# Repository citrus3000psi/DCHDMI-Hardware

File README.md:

# DCHDMI-Hardware
Hardware Design for Chriz2600 Dreamcast Firmware found at https://github.com/chriz2600/DreamcastHDMI/

This Git will include hardware version 1.3a and any future versions.

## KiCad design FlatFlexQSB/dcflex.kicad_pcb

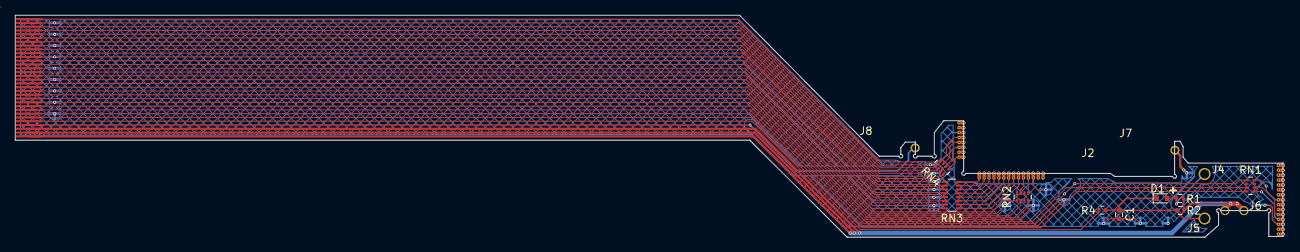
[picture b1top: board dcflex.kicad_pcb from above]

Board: 2 copper layers, 167.6 x 29.3 mm, 17 parts (0 on the bottom side), 42 nets.

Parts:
C1: .1u; C_0402
D1: 1N4148WT; D_SOD-523
J1: Conn_01x32_Male; DC_FLEX_FFC_CON
J2: Conn_01x22_Male; DC_FLEX_VIDEO_HOOKUP
J3: Conn_01x15_Male; DC_FLEX_AUDIO_HOOKUP
J4, J5, J7, J8: Conn_01x01_Female; DC-PIN6-PIN7
J6: Conn_01x02_Female; DC-3v3_power
R1, R2: 47K; R_0402
R4: 1K; R_0402
RN1, RN2, RN4: R_Pack04; R_Array_Concave_4x0402
RN3: R_Pack08; R_Array_Convex_8x0602

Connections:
/+3.3: J1.30, J1.31, J1.32, J6.1, J6.2, R1.1, R2.1
/+5: J1.29, J8.1
/ABCK: J1.24, RN1.3
/ADAT: J1.25, RN1.1
/ALRK: J1.27, RN1.4
/D0: J1.6, RN4.8
/D1: J1.7, RN3.1
/D2: J1.9, RN3.2
/D3: J1.10, RN3.3
/D4: J1.12, RN3.4
/D5: J1.13, RN3.5
/D6: J1.15, RN3.6
/D7: J1.16, RN3.7
/D8: J1.18, RN3.8
/D9: J1.19, RN2.1
/D10: J1.21, RN2.2
/D11: J1.22, RN2.4
/HSYNC: J1.4, RN4.6
/VCLK: J1.1, RN4.7
/VSYNC: J1.3, RN4.5
GND: C1.2, J1.2, J1.5, J1.8, J1.11, J1.14, J1.17, J1.20, J1.23, J1.26, J2.3, J2.20, J3.3, J7.1
unnamed: C1.1, D1.1, J5.1, R2.2, R4.1
unnamed: D1.2, J4.1, R1.2
unnamed: J1.28, R4.2
unnamed: J2.4, RN2.5
unnamed: J2.5, RN2.7
unnamed: J2.6, RN2.8
unnamed: J2.7, RN3.9
unnamed: J2.8, RN3.10
unnamed: J2.9, RN3.11
unnamed: J2.10, RN3.12
unnamed: J2.11, RN3.13
unnamed: J2.12, RN3.14
unnamed: J2.13, RN3.15
unnamed: J2.14, RN3.16
unnamed: J2.15, RN4.1
unnamed: J2.17, RN4.2
unnamed: J2.18, RN4.3
unnamed: J2.19, RN4.4
unnamed: J3.4, RN1.5
unnamed: J3.5, RN1.6
unnamed: J3.8, RN1.8

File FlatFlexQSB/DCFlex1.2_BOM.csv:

Reference, Quantity, Value, Footprint
C1 ,1,.1u 50,Capacitors_SMD:C_0402
D1 ,1, 1N4148WT-7,Diodes_SMD:D_SOD-523
R1 R2 ,2,47K,Resistors_SMD:R_0402
R4 ,1,1K,Resistors_SMD:R_0402
RN1 RN2 RN4 ,3, EXB-N8V470JX,Resistors_SMD:R_Array_Concave_4x0402
RN3 ,1, EXB-2HV470JV,Resistors_SMD:R_Array_Convex_8x0602

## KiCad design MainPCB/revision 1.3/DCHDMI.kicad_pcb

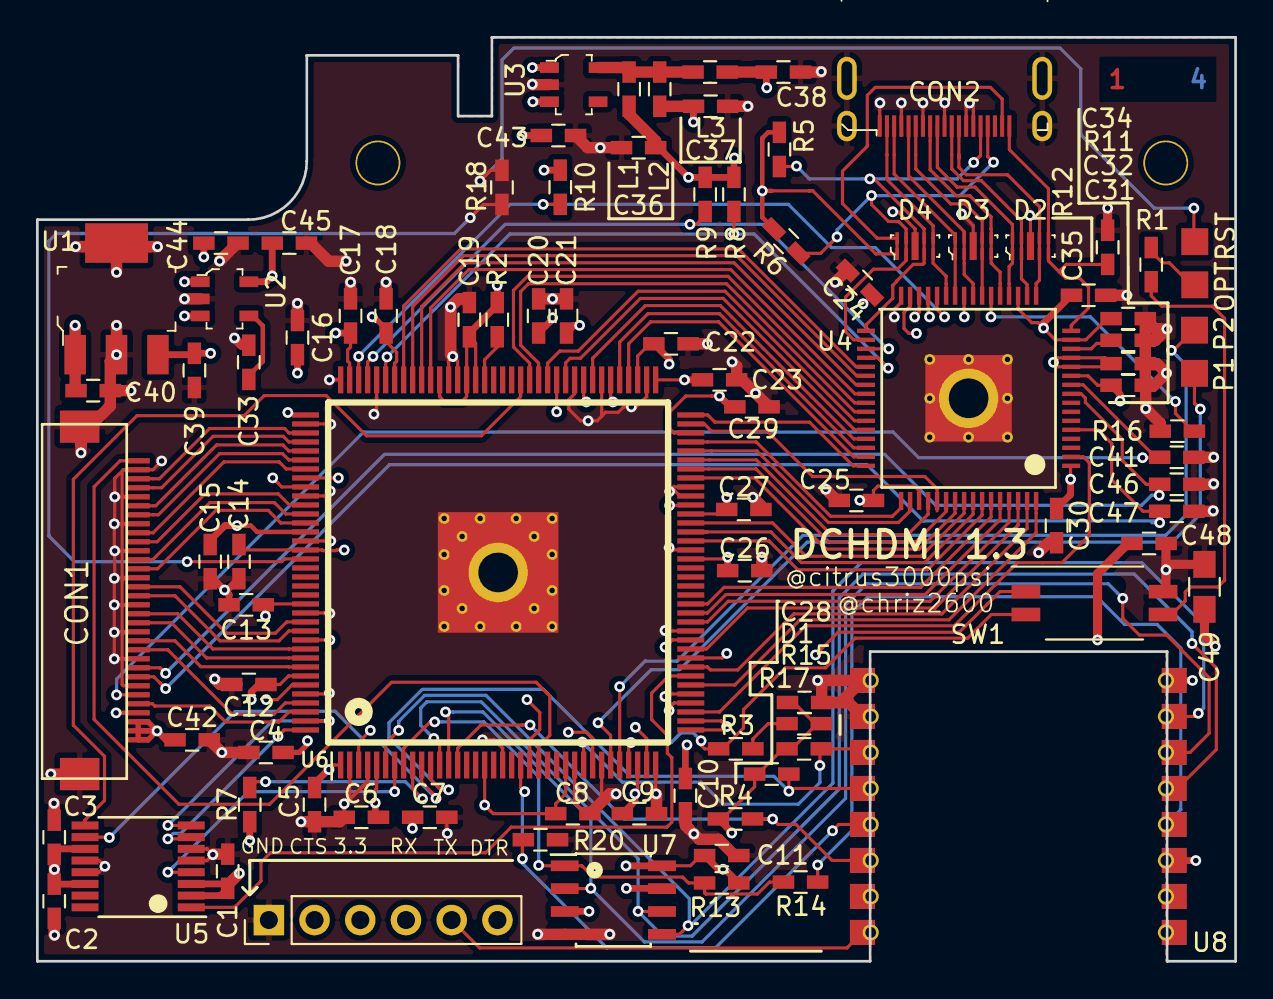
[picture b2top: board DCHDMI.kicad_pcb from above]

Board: 4 copper layers, 66.6 x 51.3 mm, 89 parts (0 on the bottom side), 100 nets.

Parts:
C1, C2, C3, C4, C5, C6, C7, C8, C9, C10, C11, C12, C13, C14, C15, C16, C17, C18, C19, C20, C21, C22, C23, C24, C25, C26, C27, C28, C29, C30, C31, C32, C34, C35, C48: .1u; C_0603_HandSoldering
C33: 470p; C_0603_HandSoldering
C36, C37, C38, C39, C40, C42, C43, C44, C45: 10u; C_0603_HandSoldering
C41, C46, C47: 47p; C_0603_HandSoldering
C49: 22u; C_0805_HandSoldering
CON1: 3-1775333-2; FPC_32
CON2: DC2R019JA7R1700
CON3: CONN_01X06; Pin_Header_Straight_1x06_Pitch2.54mm
CON4, CON5: CONN_01X03; 2_Pads_Small
D1: LED; C_0603_HandSoldering
D2, D3, D4: SP3012-04UTG; UFDFN-10_2.5x1mm
L1, L2, L3: 10u; C_0603_HandSoldering
R1, R18: 470; C_0603_HandSoldering
R2, R3, R4, R7, R12, R13, R15, R17, R20: 10K; C_0603_HandSoldering
R5, R6, R8, R9, R10, R16: 2K; C_0603_HandSoldering
R11: 880; C_0603_HandSoldering
R14: 22; C_0603_HandSoldering
SW1: SW_DIP_x02; SW_DIP_x2_W7.62mm_Slide_Copal_CHS-B
U1: MCP1826S-1202E/DB; SOT-223
U2: MIC5219-2.5YM5-TR; SOT-753
U3: LP5907MFX-1.8/NOPB; SOT-753
U4: ADV7513; LQFP-64_10x10mm_Pitch0.5mm_PAD
U5: 664G-03LF; TSSOP-16_4.4x5mm_Pitch0.65mm
U6: 10CL025; altera144_wcenterpad
U7: MX25L1606EM1I-12G; SOIC-8_3.9x4.9mm_Pitch1.27mm
U8: ESP-12E; ESP-12_FLAT

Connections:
+1.2: C5.1, C6.1, C9.1, C12.1, C14.1, C16.1, C18.1, C20.1, C23.1, C27.1, C29.1, C39.1, U1.3, U6.1, U6.5, U6.29, U6.34, U6.37, U6.38, U6.45, U6.61, U6.70, U6.73, U6.78, U6.84, U6.102, U6.109, U6.116, U6.124, U6.134, U6.138
+1.8: L1.1, L2.2, L3.2, U3.5
+2.5: C4.1, C10.1, C17.1, C22.1, C45.1, U2.5, U6.3, U6.35, U6.75, U6.107
+3V3: C1.1, C2.1, C3.1, C7.1, C8.1, C11.1, C13.1, C15.1, C19.1, C21.1, C26.1, C28.1, C40.1, C42.1, C43.1, C44.1, C48.1, C49.1, CON1.30, CON1.31, CON1.32, CON3.3, D1.2, R2.1, R4.1, R7.1, R10.2, R13.1, R15.1, R17.1, U1.1, U2.1, U2.3, U3.1, U3.3, U4.29, U5.2, U5.3, U5.11, U5.14, U6.17, U6.26, U6.40, U6.47, U6.56, U6.62, U6.81, U6.93, U6.94, U6.97, U6.117, U6.122, U6.130, U6.139, U7.3, U7.7, U7.8, U8.3, U8.8
/+5: CON1.29, CON2.18, D4.1, D4.10, R5.1, R6.1
/ABCK: C46.2, CON1.24, U4.9
/ADAT: C47.2, CON1.25, U4.5
/ADVCLK: U4.53, U6.71
/ALRK: C41.2, CON1.27, U4.10
/CLK: U5.9, U6.88
/CS: R13.2, R14.2, U6.8, U7.1
/DCLK: U6.12, U7.6, U8.5
/ESP_SCL: R17.2, SW1.1, U6.11, U8.12
/ESP_SDA: R15.2, U6.28, U8.11
/HRST: R3.1, SW1.2, U6.33
/HRST_OUT: CON5.1, R1.1
/INT: R10.1, U4.28, U6.106
/MISO: U6.13, U7.2, U8.6
/MOSI: U6.6, U7.5, U8.7
/PAD1: CON4.1, U6.31
/PAD2: CON4.2, U6.32
/RXD: CON3.4, U8.15
/S0: U5.4, U6.7
/S1: U5.10, U6.10
/S2: U5.8, U6.143
/S3: U5.7, U6.144
/SCL: R9.1, U4.35, U6.105
/SCL_H: CON2.15, D4.4, D4.7, R5.2, U4.33
/SDA: R8.1, U4.36, U6.103
/SDA_H: CON2.16, D4.2, D4.9, R6.2, U4.34
/SRST: CON5.2, R18.1
/TXD: CON3.5, U8.16
/VCLK: CON1.1, U6.23
/X1: U5.1, U6.43
/nCE: R20.1, U6.21, U8.13
/nConf: R4.2, U6.14, U8.14
GND: C1.2, C2.2, C3.2, C4.2, C5.2, C6.2, C7.2, C8.2, C9.2, C10.2, C11.2, C12.2, C13.2, C14.2, C15.2, C16.2, C17.2, C18.2, C19.2, C20.2, C21.2, C22.2, C23.2, C24.2, C25.2, C26.2, C27.2, C28.2, C29.2, C30.2, C31.2, C32.2, C33.1, C34.2, C35.2, C36.2, C37.2, C38.2, C39.2, C40.2, C41.1, C42.2, C43.2, C44.2, C45.2, C46.1, C47.1, C48.2, C49.2, CON1.2, CON1.5, CON1.8, CON1.11, CON1.14, CON1.17, CON1.20, CON1.23, CON1.26, CON2.1, CON2.4, CON2.7, CON2.10, CON2.13, CON2.14, CON2.20, CON3.1, D2.3, D2.8, D3.3, D3.8, D4.3, D4.8, R11.2, R12.2, R16.1, R20.2, SW1.4, U1.2, U1.4, U2.2, U3.2, U4.30, U4.32, U4.65, U5.5, U5.6, U5.12, U5.13, U6.2, U6.4, U6.19, U6.27, U6.30, U6.36, U6.41, U6.48, U6.57, U6.63, U6.64, U6.74, U6.79, U6.82, U6.95, U6.96, U6.104, U6.108, U6.110, U6.118, U6.123, U6.131, U6.140, U6.145, U7.4, U8.9, U8.10
unnamed: C24.1, C25.1, C30.1, C31.1, C36.1, L1.2, R8.2, R9.2, U4.1, U4.11, U4.31, U4.51
unnamed: C32.1, C38.1, L3.1, U4.12, U4.13
unnamed: C33.2, U2.4
unnamed: C34.1, C35.1, C37.1, L2.1, U4.15, U4.19, U4.25
unnamed: CON1.3, U6.111
unnamed: CON1.4, U6.112
unnamed: CON1.6, U6.113
unnamed: CON1.7, U6.114
unnamed: CON1.9, U6.115
unnamed: CON1.10, U6.119
unnamed: CON1.12, U6.120
unnamed: CON1.13, U6.121
unnamed: CON1.15, U6.132
unnamed: CON1.16, U6.133
unnamed: CON1.18, U6.135
unnamed: CON1.19, U6.136
unnamed: CON1.21, U6.137
unnamed: CON1.22, U6.141
unnamed: CON1.28, U6.142
unnamed: CON2.2, D4.5, D4.6, U4.27
unnamed: CON2.3, D3.1, D3.10, U4.26
unnamed: CON2.5, D3.2, D3.9, U4.24
unnamed: CON2.6, D3.4, D3.7, U4.23
unnamed: CON2.8, D3.5, D3.6, U4.21
unnamed: CON2.9, D2.1, D2.10, U4.20
unnamed: CON2.11, D2.2, D2.9, U4.18
unnamed: CON2.12, D2.4, D2.7, U4.17
unnamed: CON2.19, D2.5, D2.6, R12.1, U4.16
unnamed: D1.1, R3.2
unnamed: R1.2, SW1.3
unnamed: R2.2, U6.92
unnamed: R7.2, U6.9
unnamed: R11.1, U4.14
unnamed: R14.1, U8.4
unnamed: R16.2, U4.22
unnamed: R18.2, U6.125
unnamed: U4.2, U6.39
unnamed: U4.37, U6.101
unnamed: U4.38, U6.100
unnamed: U4.39, U6.99
unnamed: U4.40, U6.98
unnamed: U4.41, U6.87
unnamed: U4.42, U6.86
unnamed: U4.43, U6.85
unnamed: U4.44, U6.83
unnamed: U4.45, U6.80
unnamed: U4.46, U6.77
unnamed: U4.47, U6.76
unnamed: U4.48, U6.72
unnamed: U4.49, U6.69
unnamed: U4.50, U6.68
unnamed: U4.52, U6.67
unnamed: U4.54, U6.66
unnamed: U4.55, U6.65
unnamed: U4.56, U6.60
unnamed: U4.57, U6.59
unnamed: U4.58, U6.58
unnamed: U4.59, U6.51
unnamed: U4.60, U6.50
unnamed: U4.61, U6.49
unnamed: U4.62, U6.46
unnamed: U4.63, U6.44
unnamed: U4.64, U6.42

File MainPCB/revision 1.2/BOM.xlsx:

QTY | Reference | Value | Notes
1 | BUT1 | TL3315NF100Q
34 | C1, C2, C3, C4, C5, C6, C7, C8, C9, C10, C11, C12, C13, C14, C15, C16, C17, C18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 | .1u | 0603
9 | C36, C37, C38, C39, C40, C42, C43, C44, C45 | 10u | 0603
1 | C41 | 470p | 0603
1 | CON1 | 3-1775333-2
1 | CON2 | 2013978-1
1 | D1 | LED | 0603
3 | D2, D3, D4 | SP3012-04UTG
3 | L1, L2, L3 | MLZ1608N100LT000
4 | R1, R2, R4, R12 | 10K | 0603
1 | R3 | 100 | 0603
6 | R5, R6, R7, R8, R9, R10 | 2K | 0603
1 | R11 | 887 | 0603 1%
1 | U1 | MCP1826S-1202E/DB-ND
1 | U2 | MIC5219-2.5YM5-TR
1 | U3 | LP5907MFX-1.8/NOPB
1 | U4 | ADV7513
1 | U5 | ICS664-03
1 | U6 | EP4CE6 / 10CL016 / 10CL025
1 | U7 | MX25L1606EM1I-12G
1 | R16 | 2K2 | 0603

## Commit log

2018-03-27 Added Project Files
2018-03-27 Clean Up
2018-04-05 New Revision
2018-04-05 Added 1.2a
2018-04-05 Added BOM
2018-04-23 Added 1.2b
2018-04-26 Added 1.2c
2018-05-01 Added 1.2d
2018-07-05 4 layer version
2018-07-05 solve silkscreen issues introduced with 4 layer version
2018-07-06 Increased version number
2018-07-06 Increased version
2018-07-16 Minor Update to Edge Cuts
2018-07-17 Edge Cuts Again
2018-08-16 Added ESP FTDI Header
2018-09-04 1.2 Revison
    JTAG replaced with ESP header. In Game Reset Pads added.
2018-09-05 Added 470 series resistor
2018-09-06 Fixed Issue
2018-12-21 updated to 1.3a
2019-04-15 Added Flex Design
